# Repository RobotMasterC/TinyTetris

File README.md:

# TinyTetris

A small console that plays Tetris that is powered by an Attiny85

## Demo
[Wokwi Simulation](https://wokwi.com/projects/443390022396922881)
*This will run faster than the actual hardware* 

[KiCanvas PCB](https://kicanvas.org/?github=https%3A%2F%2Fgithub.com%2FRobotMasterC%2FTinyTetris%2Fblob%2Fmain%2FPCB%2520Files%2FTinyTetris.kicad_pcb)

## BOM
- 1x Attiny85-20u
- 1x 128x32 I2C screen
- 3x Buttons
- 1x Power Switch
- 1x 3024 Button Battery Holder (For 2032 Battery)

## Images
- PCB Schematic

- PCB Overall

- PCB Front

- PCB Back

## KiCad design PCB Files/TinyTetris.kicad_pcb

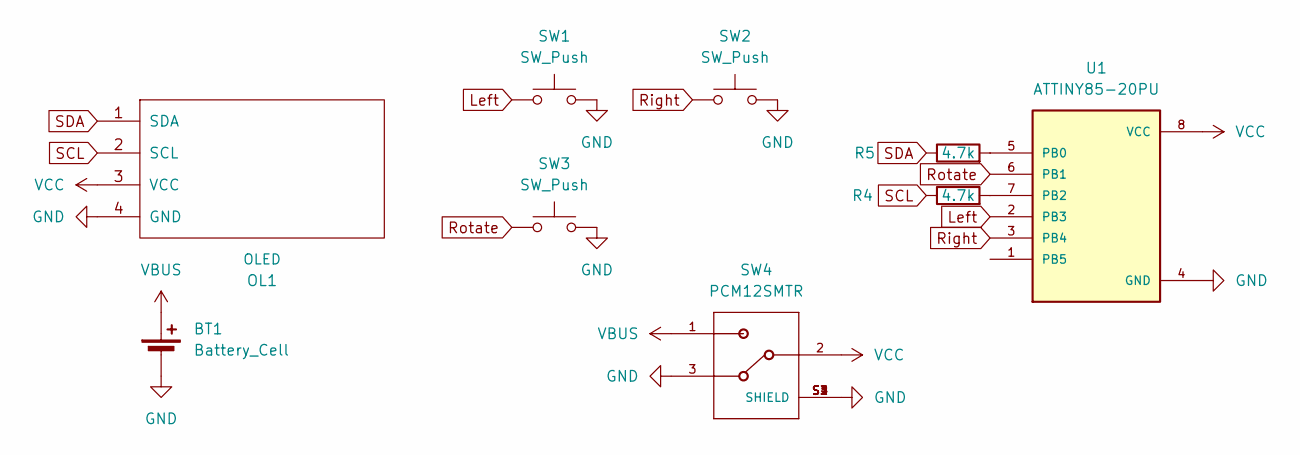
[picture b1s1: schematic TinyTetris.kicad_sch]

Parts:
BT1: Battery_Cell; BatteryHolder_Keystone_3034_1x20mm
OL1: OLED
R4, R5: 4.7k; R_0402_1005Metric
SW1, SW2, SW3: SW_Push; SW_PUSH_6mm_H4.3mm
SW4: PCM12SMTR; SW_PCM12SMTR
U1: ATTINY85-20PU; DIP762W46P254L927H533Q8B

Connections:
GND: BT1.2 (-), OL1.4 (GND), SW1.2, SW2.2, SW3.2, SW4.3, SW4.S1 (SHIELD), SW4.S2 (SHIELD), SW4.S3 (SHIELD), SW4.S4 (SHIELD), U1.4 (GND)
Left: SW1.1, U1.2 (PB3)
unnamed: R5.2, U1.5 (PB0)
unnamed: R4.2, U1.7 (PB2)
Right: SW2.1, U1.3 (PB4)
Rotate: SW3.1, U1.6 (PB1)
SCL: OL1.2 (SCL), R4.1
SDA: OL1.1 (SDA), R5.1
VBUS: BT1.1 (+), SW4.1
VCC: OL1.3 (VCC), SW4.2, U1.8 (VCC)

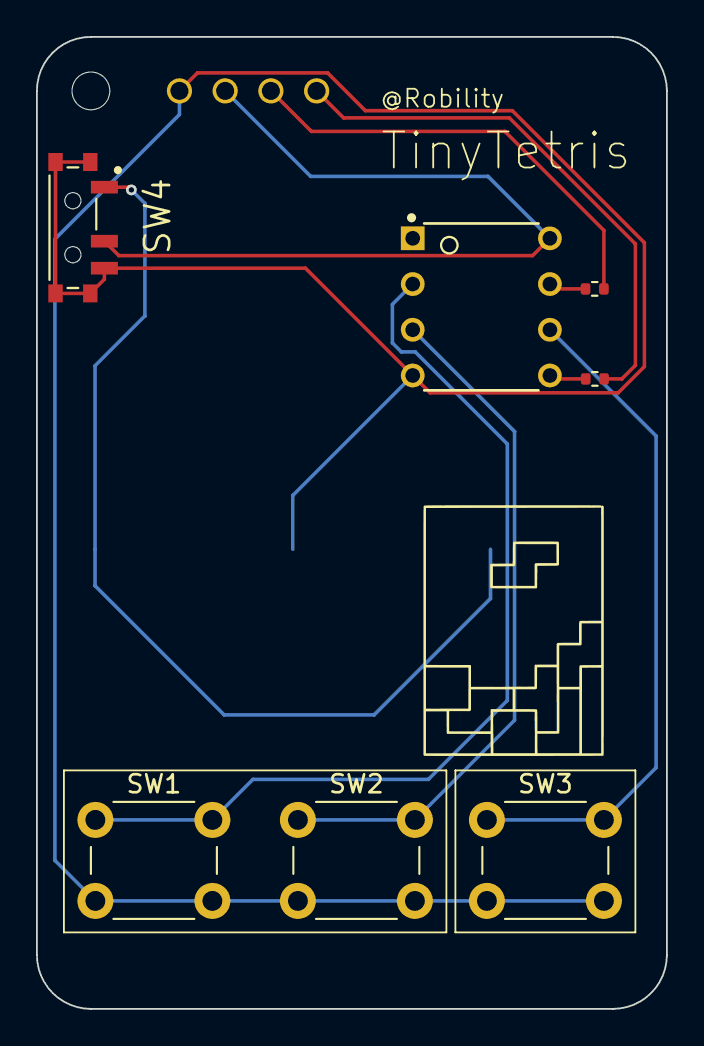
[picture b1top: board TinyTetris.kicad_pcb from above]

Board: 2 copper layers, 35.0 x 54.0 mm, 9 parts (1 on the bottom side), 10 nets.

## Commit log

2025-10-23 Update PCB Files
    The PCB is thinner, the power LED was removed, and the power switch is a different type
2025-10-23 Update Images for new PCB
2025-10-23 Update README for new PCB
